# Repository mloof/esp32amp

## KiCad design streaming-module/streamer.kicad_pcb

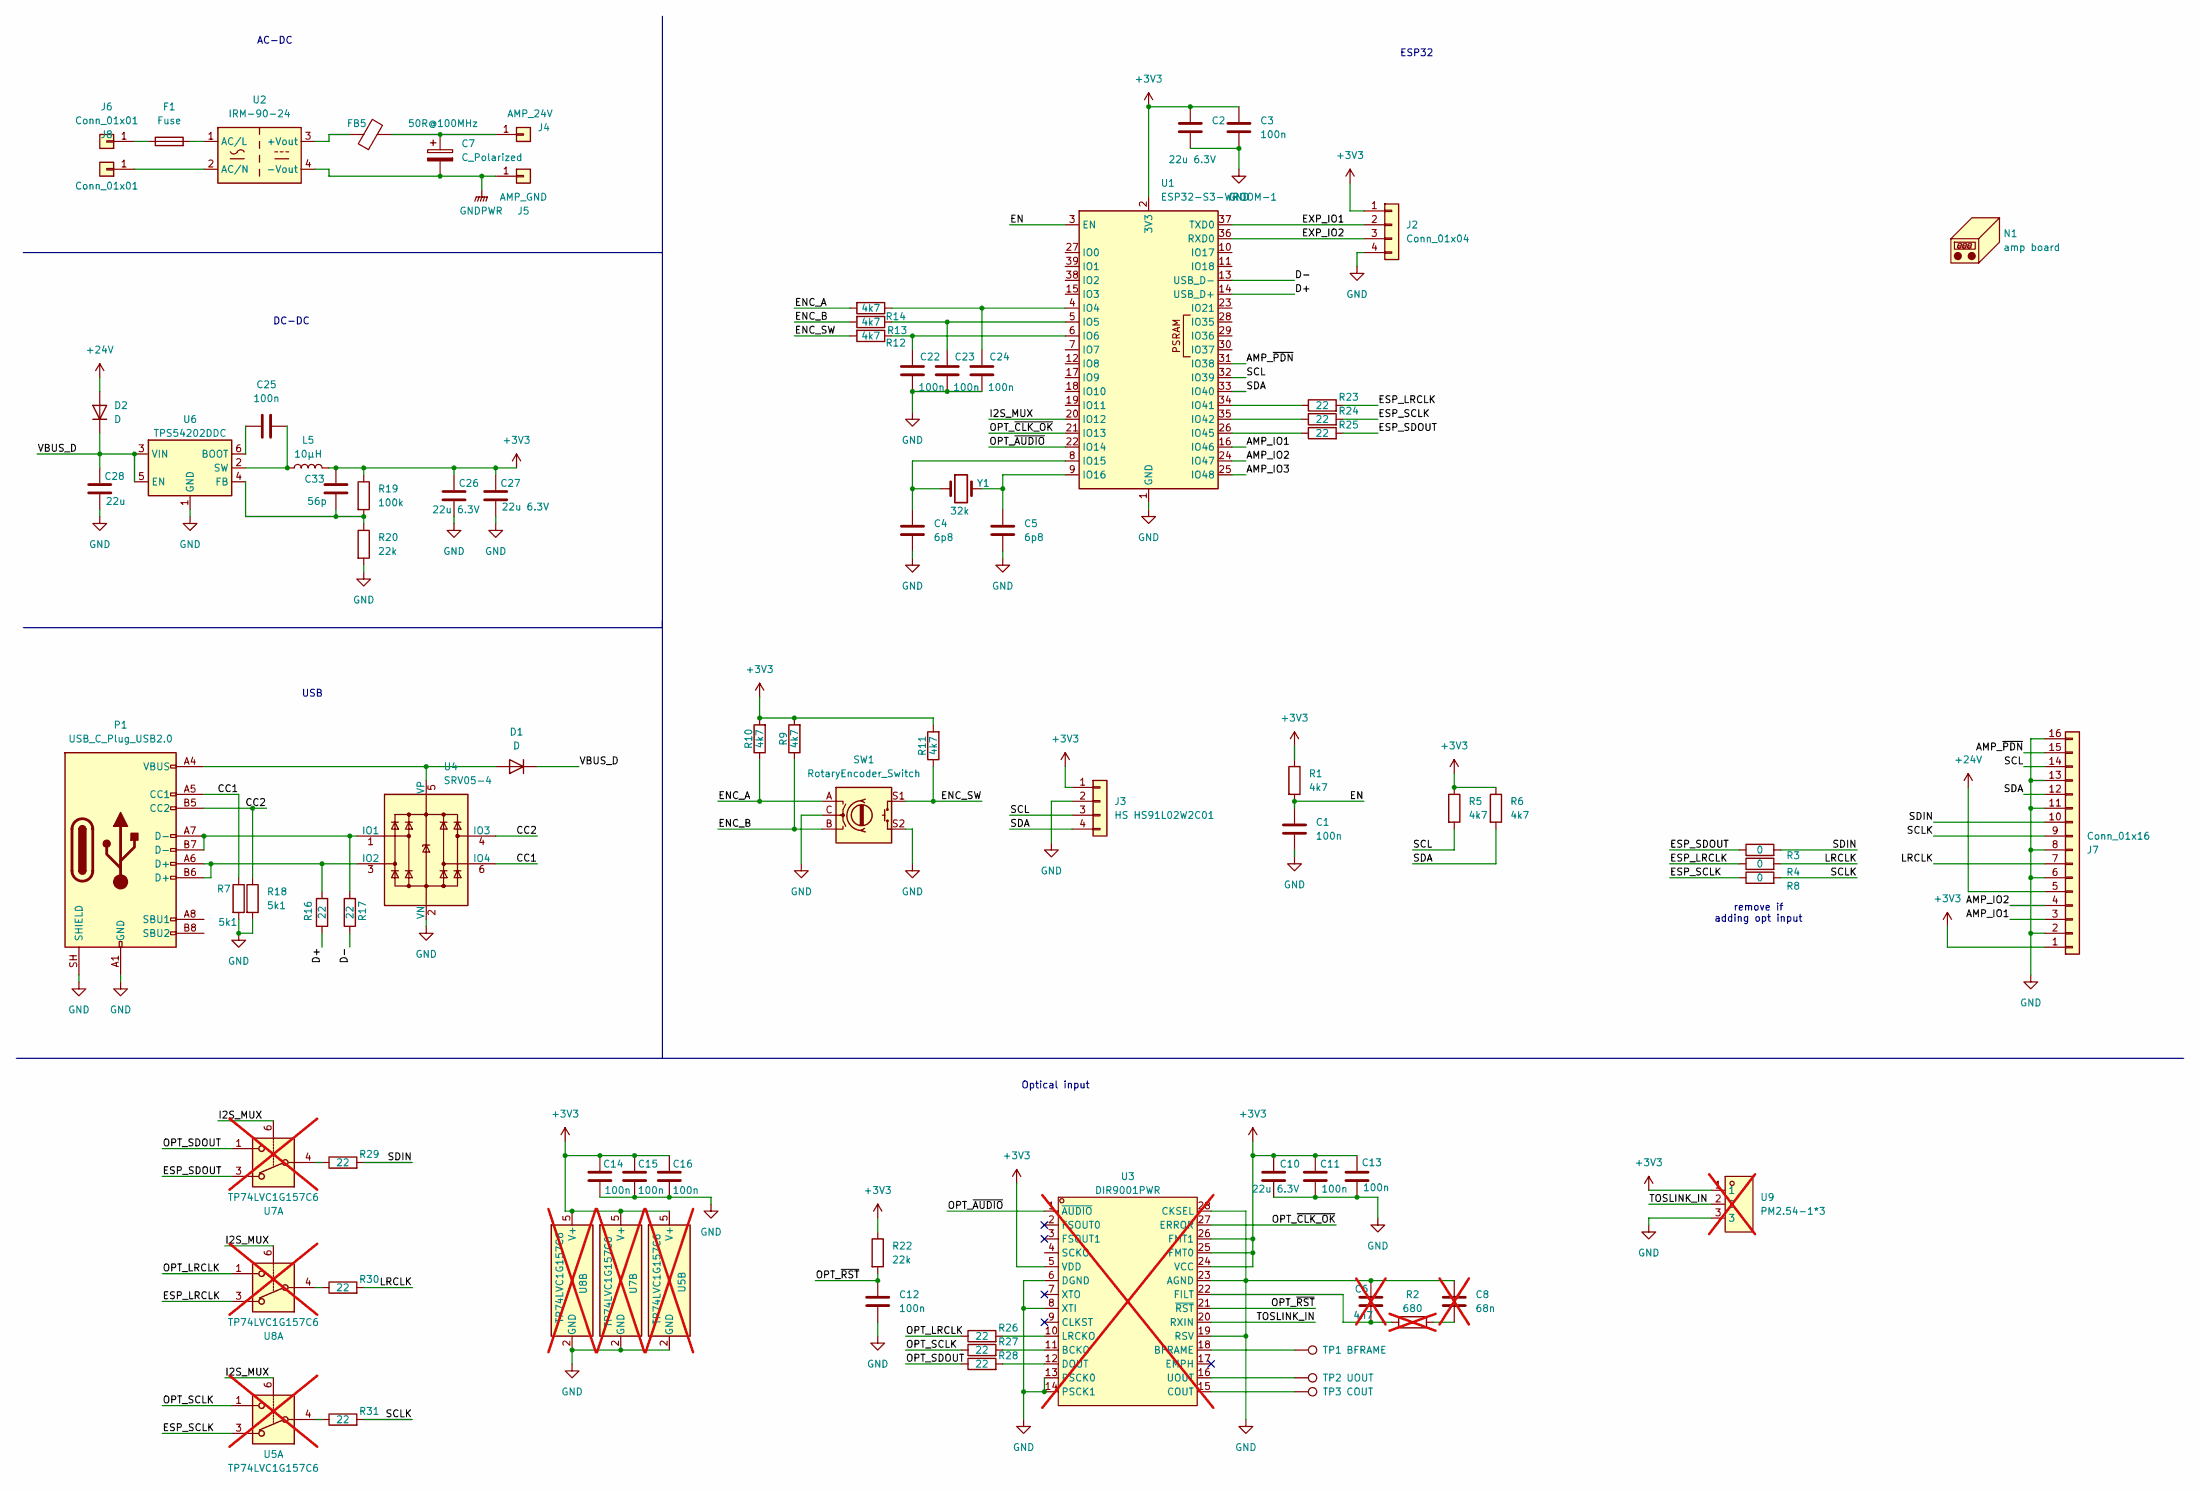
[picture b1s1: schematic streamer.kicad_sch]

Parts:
C1, C3, C11, C12, C13, C14, C15, C16, C22, C23, C24, C25: 100n; C_0402_1005Metric; JLC C307331
C2, C10, C26, C27: 22u 6.3V; C_0805_2012Metric; JLC C5674
C4, C5: 6p8; C_0402_1005Metric; JLC C1576
C6: 4n7; C_0603_1608Metric; JLC C1518204; not fitted
C7: C_Polarized; CP_Radial_D8.0mm_P3.50mm; JLC C52994591
C8: 68n; C_1206_3216Metric; JLC C77084; not fitted
C28: 22u; C_0805_2012Metric; Voltage ratin 25V; JLC C45783
C33: 56p; C_0603_1608Metric; JLC C39148
D1, D2: D; Nexperia_CFP3_SOD-123W; JLC C8598
F1: Fuse; Fuse_2512_6332Metric; JLC C2762422
FB5: 50R@100MHz; L_1206_3216Metric; JLC C710524
J2: Conn_01x04; PinHeader_1x04_P2.54mm_Vertical
J3: HS HS91L02W2C01; PinHeader_1x04_P2.54mm_Vertical
J4: AMP_24V; SolderWire-2.5sqmm_1x01_D2.4mm_OD3.6mm
J5: AMP_GND; SolderWire-2.5sqmm_1x01_D2.4mm_OD3.6mm
J6, J8: Conn_01x01; SolderWire-1.5sqmm_1x01_D1.7mm_OD3mm
J7: Conn_01x16; 5034801600; JLC C5510131
L5: 10µH; L_APV_ANR6028; JLC C2849524
N1: amp board; virtual_component
P1: USB_C_Plug_USB2.0; USB-C-SMD_GT-USB-7058; JLC C2894897
R1, R5, R6, R9, R10, R11, R12, R13, R14: 4k7; R_0402_1005Metric; JLC C25900
R2: 680; R_0402_1005Metric; JLC C28566373; not fitted
R3, R4, R8: 0; R_0402_1005Metric; JLC C17168
R7, R18: 5k1; R_0402_1005Metric; JLC C25905
R16, R17, R23, R24, R25, R26, R27, R28, R29, R30, R31: 22; R_0402_1005Metric; JLC C25092
R19: 100k; R_0402_1005Metric; JLC C25741
R20, R22: 22k; R_0402_1005Metric; JLC C25768
SW1: RotaryEncoder_Switch; Rotary encoder; JLC C18213469
TP1: BFRAME; TestPoint_Pad_2.0x2.0mm
TP2: UOUT; TestPoint_Pad_2.0x2.0mm
TP3: COUT; TestPoint_Pad_2.0x2.0mm
U1: ESP32-S3-WROOM-1; JLC C2913202
U2: IRM-90-24; Converter_ACDC_MeanWell_IRM-60-xx_THT
U3: DIR9001PWR; TSSOP-28_L9.7-W4.4-P0.65-LS6.4-BL; MPN DIR9001PWR; LCSC Part C96215; not fitted
U4: SRV05-4; SOT-23-6
U5, U7, U8: TP74LVC1G157C6; SOT-363_SC-70-6; JLC C46473012; not fitted
U6: TPS54202DDC; SOT-23-6; JLC C191884
U9: PM2.54-1*3; HDR-TH_3P-P2.54-V-F; MPN PM2.54-1*3; LCSC Part C5116529; not fitted
Y1: 32k; Crystal_SMD_3215-2Pin_3.2x1.5mm; JLC C1985240

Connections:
+3V3: C2.1, C3.1, C10.1, C11.1, C13.1, C14.1, C15.1, C16.1, C26.1, C27.1, C33.1, J2.1, J3.1, J7.1, L5.2, R1.1, R5.1, R6.1, R9.2, R10.2, R11.2, R19.1, R22.1, U1.2 (3V3), U3.5 (VDD), U3.24 (VCC), U3.25 (FMT0), U3.26 (FMT1), U5.5 (V+), U7.5 (V+), U8.5 (V+), U9.1
+24V: D2.2 (A), J7.5
/AMP_IO1: J7.3, U1.16 (IO46)
/AMP_IO2: J7.4, U1.24 (IO47)
/AMP_IO3: U1.25 (IO48)
/AMP_~PDN: J7.15, U1.31 (IO38)
/CC1: P1.A5 (CC1), R7.1, U4.6 (IO4)
/CC2: P1.B5 (CC2), R18.1, U4.4 (IO3)
/D+: R16.1, U1.14 (USB_D+)
/D-: R17.1, U1.13 (USB_D-)
/EN: C1.1, R1.2, U1.3 (EN)
/ENC_A: R10.1, R14.2, SW1.A
/ENC_B: R9.1, R13.2, SW1.B
/ENC_SW: R11.1, R12.2, SW1.S1
/ESP_LRCLK: R4.1, R23.2, U8.3
/ESP_SCLK: R8.1, R24.2, U5.3
/ESP_SDOUT: R3.1, R25.2, U7.3
/EXP_IO1: J2.2, U1.37 (TXD0)
/EXP_IO2: J2.3, U1.36 (RXD0)
/I2S_MUX: U1.20 (IO12), U5.6, U7.6, U8.6
/LRCLK: J7.7, R4.2, R30.2
/OPT_LRCLK: R26.1, U8.1
/OPT_SCLK: R27.1, U5.1
/OPT_SDOUT: R28.1, U7.1
/OPT_~AUDIO: U1.22 (IO14), U3.1 (~AUDIO)
/OPT_~CLK_OK: U1.21 (IO13), U3.27 (ERROR)
/OPT_~RST: C12.1, R22.2, U3.21 (~RST)
/SCL: J3.3, J7.14, R5.2, U1.32 (IO39)
/SCLK: J7.9, R8.2, R31.2
/SDA: J3.4, J7.12, R6.2, U1.33 (IO40)
/SDIN: J7.10, R3.2, R29.2
/TOSLINK_IN: U3.20 (RXIN), U9.2
/VBUS_D: C28.1, D1.1 (K), D2.1 (K), U6.3 (VIN), U6.5 (EN)
GND: C1.2, C2.2, C3.2, C4.2, C5.2, C6.1, C8.1, C10.2, C11.2, C12.2, C13.2, C14.2, C15.2, C16.2, C22.2, C23.2, C24.2, C26.2, C27.2, C28.2, J2.4, J3.2, J7.2, J7.6, J7.8, J7.11, J7.13, J7.16, P1.A1 (GND), P1.A12 (GND), P1.B1 (GND), P1.B12 (GND), P1.SH (SHIELD), R7.2, R18.2, R20.2, SW1.C, SW1.S2, U1.1 (GND), U1.40 (GND), U1.41 (GND), U3.6 (DGND), U3.8 (XTI), U3.13 (PSCK0), U3.14 (PSCK1), U3.19 (RSV), U3.23 (AGND), U3.28 (CKSEL), U4.2 (VN), U5.2 (GND), U6.1 (GND), U7.2 (GND), U8.2 (GND), U9.3
GNDPWR: C7.2, J5.1 (Pin_1_1), U2.4 (-Vout)
unnamed: C8.2, R2.2
unnamed: D1.2 (A), P1.A4 (VBUS), P1.A9 (VBUS), P1.B4 (VBUS), P1.B9 (VBUS), U4.5 (VP)
unnamed: C7.1, FB5.2, J4.1 (Pin_1_1)
unnamed: F1.1, J6.1 (Pin_1_1)
unnamed: J8.1 (Pin_1_1), U2.2 (AC/N)
unnamed: R29.1, U7.4
unnamed: R30.1, U8.4
unnamed: R31.1, U5.4
unnamed: C24.1, R14.1, U1.4 (IO4)
unnamed: C23.1, R13.1, U1.5 (IO5)
unnamed: C22.1, R12.1, U1.6 (IO6)
unnamed: C4.1, U1.8 (IO15), Y1.1
unnamed: C5.1, U1.9 (IO16), Y1.2
unnamed: R23.1, U1.34 (IO41)
unnamed: R24.1, U1.35 (IO42)
unnamed: R25.1, U1.26 (IO45)
unnamed: FB5.1, U2.3 (+Vout)
unnamed: F1.2, U2.1 (AC/L)
unnamed: R27.2, U3.11 (BCKO)
unnamed: TP1.1 (1_1), U3.18 (BFRAME)
unnamed: TP3.1 (1_1), U3.15 (COUT)
unnamed: R28.2, U3.12 (DOUT)
unnamed: C6.2, R2.1, U3.22 (FILT)
unnamed: R26.2, U3.10 (LRCKO)
unnamed: TP2.1 (1_1), U3.16 (UOUT)
unnamed: P1.A7 (D-), P1.B7 (D-), R17.2, U4.1 (IO1)
unnamed: P1.A6 (D+), P1.B6 (D+), R16.2, U4.3 (IO2)
unnamed: C25.2, U6.6 (BOOT)
unnamed: C33.2, R19.2, R20.1, U6.4 (FB)
unnamed: C25.1, L5.1, U6.2 (SW)

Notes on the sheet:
USB
remove if adding opt input
ESP32
Optical input
DC-DC
AC-DC

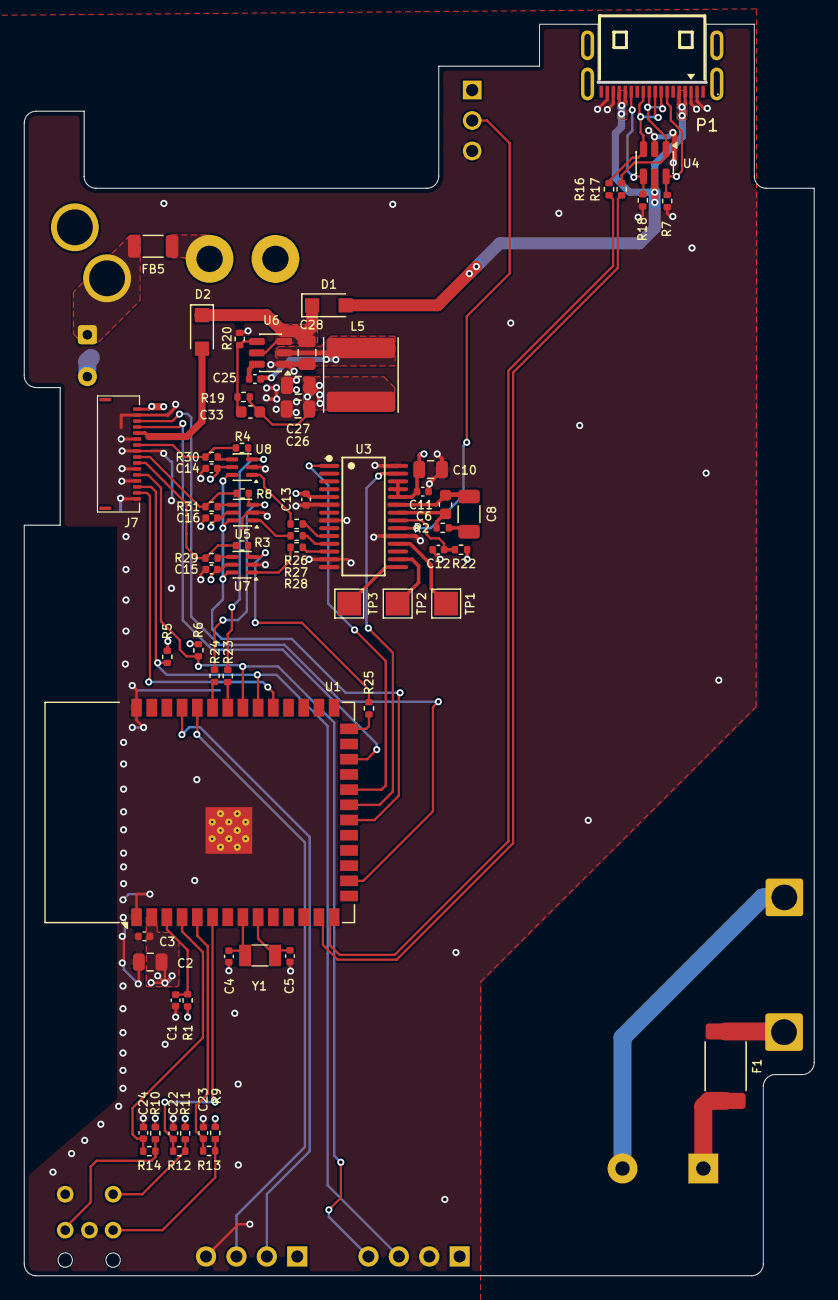
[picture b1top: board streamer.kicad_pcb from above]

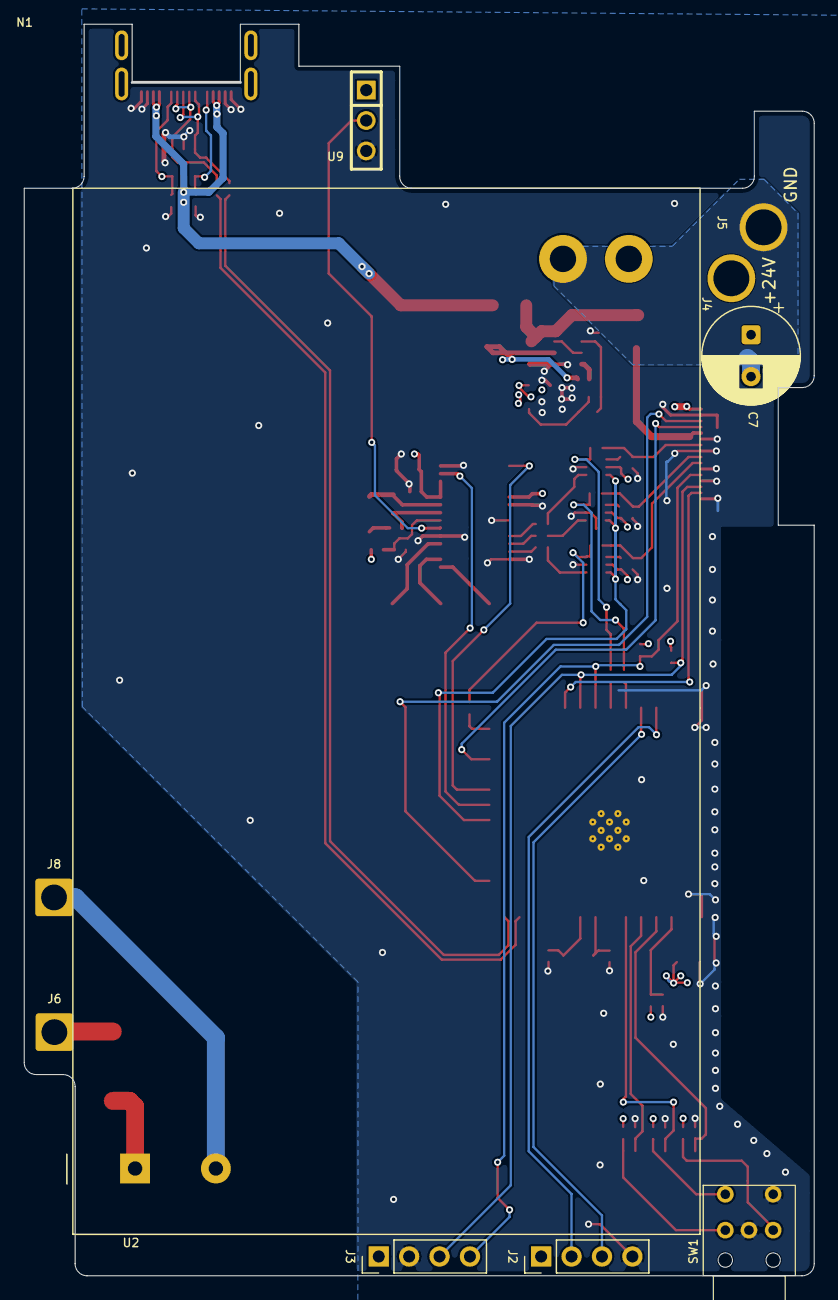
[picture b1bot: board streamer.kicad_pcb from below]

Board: 4 copper layers, 66.0 x 104.6 mm, 80 parts (11 on the bottom side), 64 nets.

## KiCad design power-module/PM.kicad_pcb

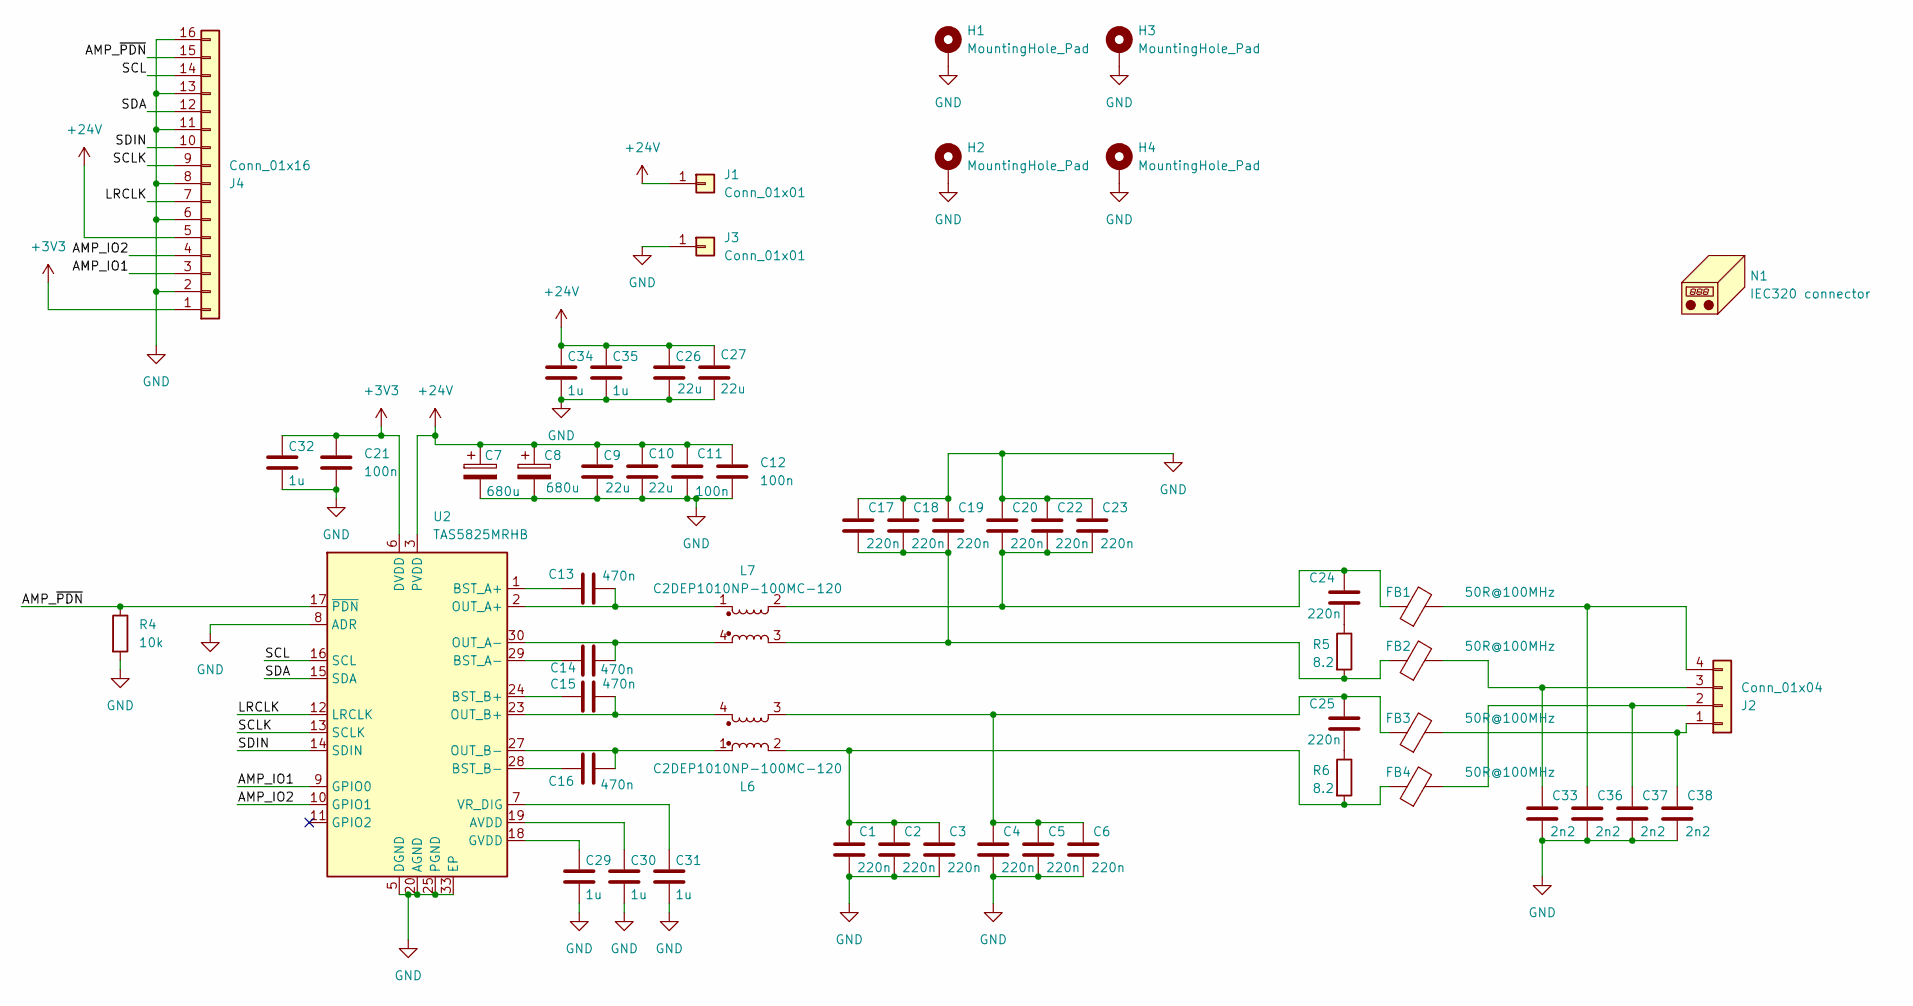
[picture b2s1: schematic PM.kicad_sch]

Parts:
C1, C2, C3, C4, C5, C6, C17, C18, C19, C20, C22, C23, C24, C25: 220n; C_1206_3216Metric; JLC C464977
C7, C8: 680u; CP_Elec_10x10.5; JLC C44606610
C9, C10, C26, C27: 22u; C_0805_2012Metric; Voltage rating 25V; JLC C45783
C11, C12, C21: 100n; C_0402_1005Metric; JLC C307331
C13, C14, C15, C16: 470n; C_0603_1608Metric; JLC C77572
C29, C30, C31, C32: 1u; C_0402_1005Metric; JLC C52923
C33, C36, C37, C38: 2n2; C_0603_1608Metric; JLC C33353
C34, C35: 1u; C_0603_1608Metric; JLC C15849
FB1, FB2, FB3, FB4: 50R@100MHz; L_1206_3216Metric; JLC C710524
H1, H2, H3, H4: MountingHole_Pad; MountingHole_2.7mm
J1, J3: Conn_01x01; SolderWirePad_1x01_SMD_3x6mm
J2: Conn_01x04; MX25C-7.62-04P; JLC C5188511
J4: Conn_01x16; 5034801600; JLC C5510131
L6, L7: C2DEP1010NP-100MC-120; C2DEP1010; JLC C171571
N1: IEC320 connector; virtual_component
R4: 10k; R_0402_1005Metric; JLC C25744
R5, R6: 8.2; R_1206_3216Metric; JLC C6301234
U2: TAS5825MRHB; Texas_RHB0032E_VQFN-32-1EP_5x5mm_P0.5mm_EP3.45x3.45mm_Therm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; JLC C471049

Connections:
+3V3: C21.1, C32.1, J4.1, U2.6 (DVDD)
+24V: C7.1, C8.1, C9.1, C10.1, C11.1, C12.1, C26.1, C27.1, C34.1, C35.1, J1.1 (Pin_1_1), J4.5, U2.3 (PVDD), U2.4 (PVDD), U2.21 (PVDD), U2.22 (PVDD)
/AMP_IO1: J4.3, U2.9 (GPIO0)
/AMP_IO2: J4.4, U2.10 (GPIO1)
/AMP_~PDN: J4.15, R4.1, U2.17 (~PDN)
/LRCLK: J4.7, U2.12 (LRCLK)
/SCL: J4.14, U2.16 (SCL)
/SCLK: J4.9, U2.13 (SCLK)
/SDA: J4.12, U2.15 (SDA)
/SDIN: J4.10, U2.14 (SDIN)
GND: C1.2, C2.2, C3.2, C4.2, C5.2, C6.2, C7.2, C8.2, C9.2, C10.2, C11.2, C12.2, C17.1, C18.1, C19.1, C20.1, C21.2, C22.1, C23.1, C26.2, C27.2, C29.2, C30.2, C31.2, C32.2, C33.2, C34.2, C35.2, C36.2, C37.2, C38.2, H1.1, H2.1, H3.1, H4.1, J3.1 (Pin_1_1), J4.2, J4.6, J4.8, J4.11, J4.13, J4.16, R4.2, U2.5 (DGND), U2.8 (ADR), U2.20 (AGND), U2.25 (PGND), U2.26 (PGND), U2.31 (PGND), U2.32 (PGND), U2.33 (EP)
unnamed: C1.1, C2.1, C3.1, FB4.1, L6.2, R6.2
unnamed: C17.2, C18.2, C19.2, FB2.1, L7.3, R5.2
unnamed: C20.2, C22.2, C23.2, C24.1, FB1.1, L7.2
unnamed: C24.2, R5.1
unnamed: C4.1, C5.1, C6.1, C25.1, FB3.1, L6.3
unnamed: C25.2, R6.1
unnamed: C38.1, FB3.2, J2.1
unnamed: C37.1, FB4.2, J2.2
unnamed: C33.1, FB2.2, J2.3
unnamed: C36.1, FB1.2, J2.4
unnamed: C30.1, U2.19 (AVDD)
unnamed: C13.1, U2.1 (BST_A+)
unnamed: C14.1, U2.29 (BST_A-)
unnamed: C15.1, U2.24 (BST_B+)
unnamed: C16.1, U2.28 (BST_B-)
unnamed: C29.1, U2.18 (GVDD)
unnamed: C13.2, L7.1, U2.2 (OUT_A+)
unnamed: C14.2, L7.4, U2.30 (OUT_A-)
unnamed: C15.2, L6.4, U2.23 (OUT_B+)
unnamed: C16.2, L6.1, U2.27 (OUT_B-)
unnamed: C31.1, U2.7 (VR_DIG)

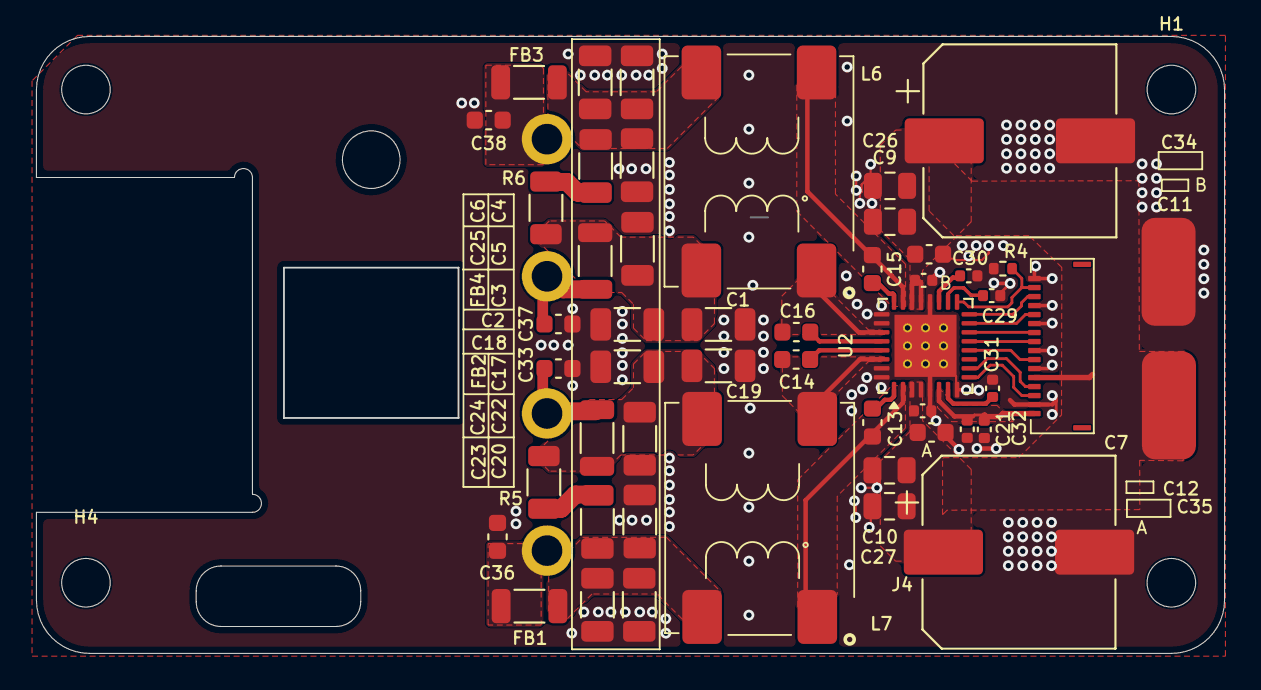
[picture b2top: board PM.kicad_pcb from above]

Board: 4 copper layers, 66.0 x 34.3 mm, 56 parts (1 on the bottom side), 32 nets.

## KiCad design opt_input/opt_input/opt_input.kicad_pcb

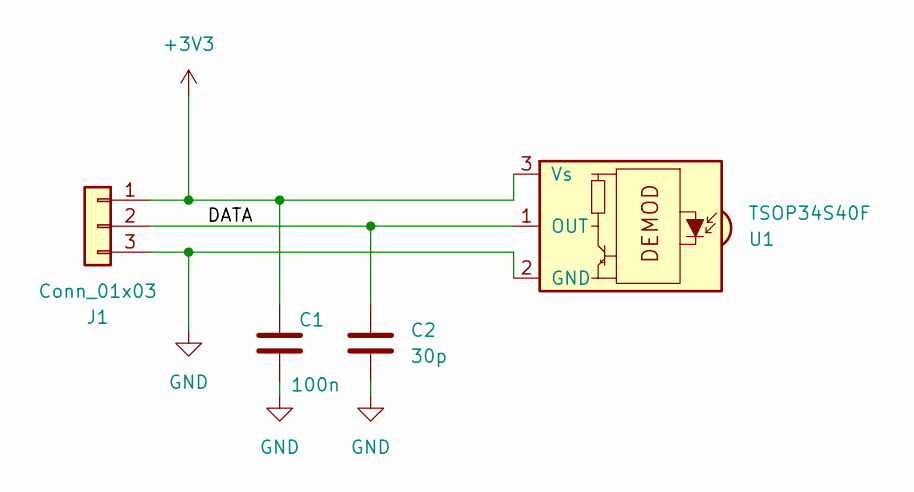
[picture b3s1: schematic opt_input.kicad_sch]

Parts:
C1: 100n; C_0402_1005Metric
C2: 30p; C_0402_1005Metric
J1: Conn_01x03; PinHeader_1x03_P2.54mm_Vertical
U1: TSOP34S40F; FCR684218R

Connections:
+3V3: C1.1, J1.1, U1.3 (Vs)
/DATA: C2.1, J1.2, U1.1 (OUT)
GND: C1.2, C2.2, J1.3, U1.2 (GND)

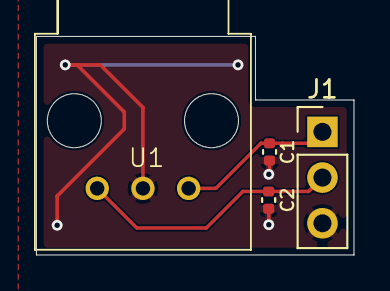
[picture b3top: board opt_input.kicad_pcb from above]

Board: 2 copper layers, 17.6 x 12.1 mm, 4 parts (0 on the bottom side), 3 nets.
